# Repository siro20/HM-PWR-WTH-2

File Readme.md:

# HM-PWR-WTH2

Open Source kicad Homematic Homebrew PCB for HmIP-WTH-2.

The PCB supports an input voltage of 3.3V - 36V and generates 2.9V on the
battery emulator clamps. It features a micro USB connector and a JST 2pin
connector.

A LED indicates if the board is working and generates a minimum current
required for stability of the LT3080 regulator.

## Schematics

[HM-PWR-WTH-2.pdf](./HM-PWR-WTH-2/HM-PWR-WTH-2.pdf)

## Pictures

** Mounting plate **

** Assembled **

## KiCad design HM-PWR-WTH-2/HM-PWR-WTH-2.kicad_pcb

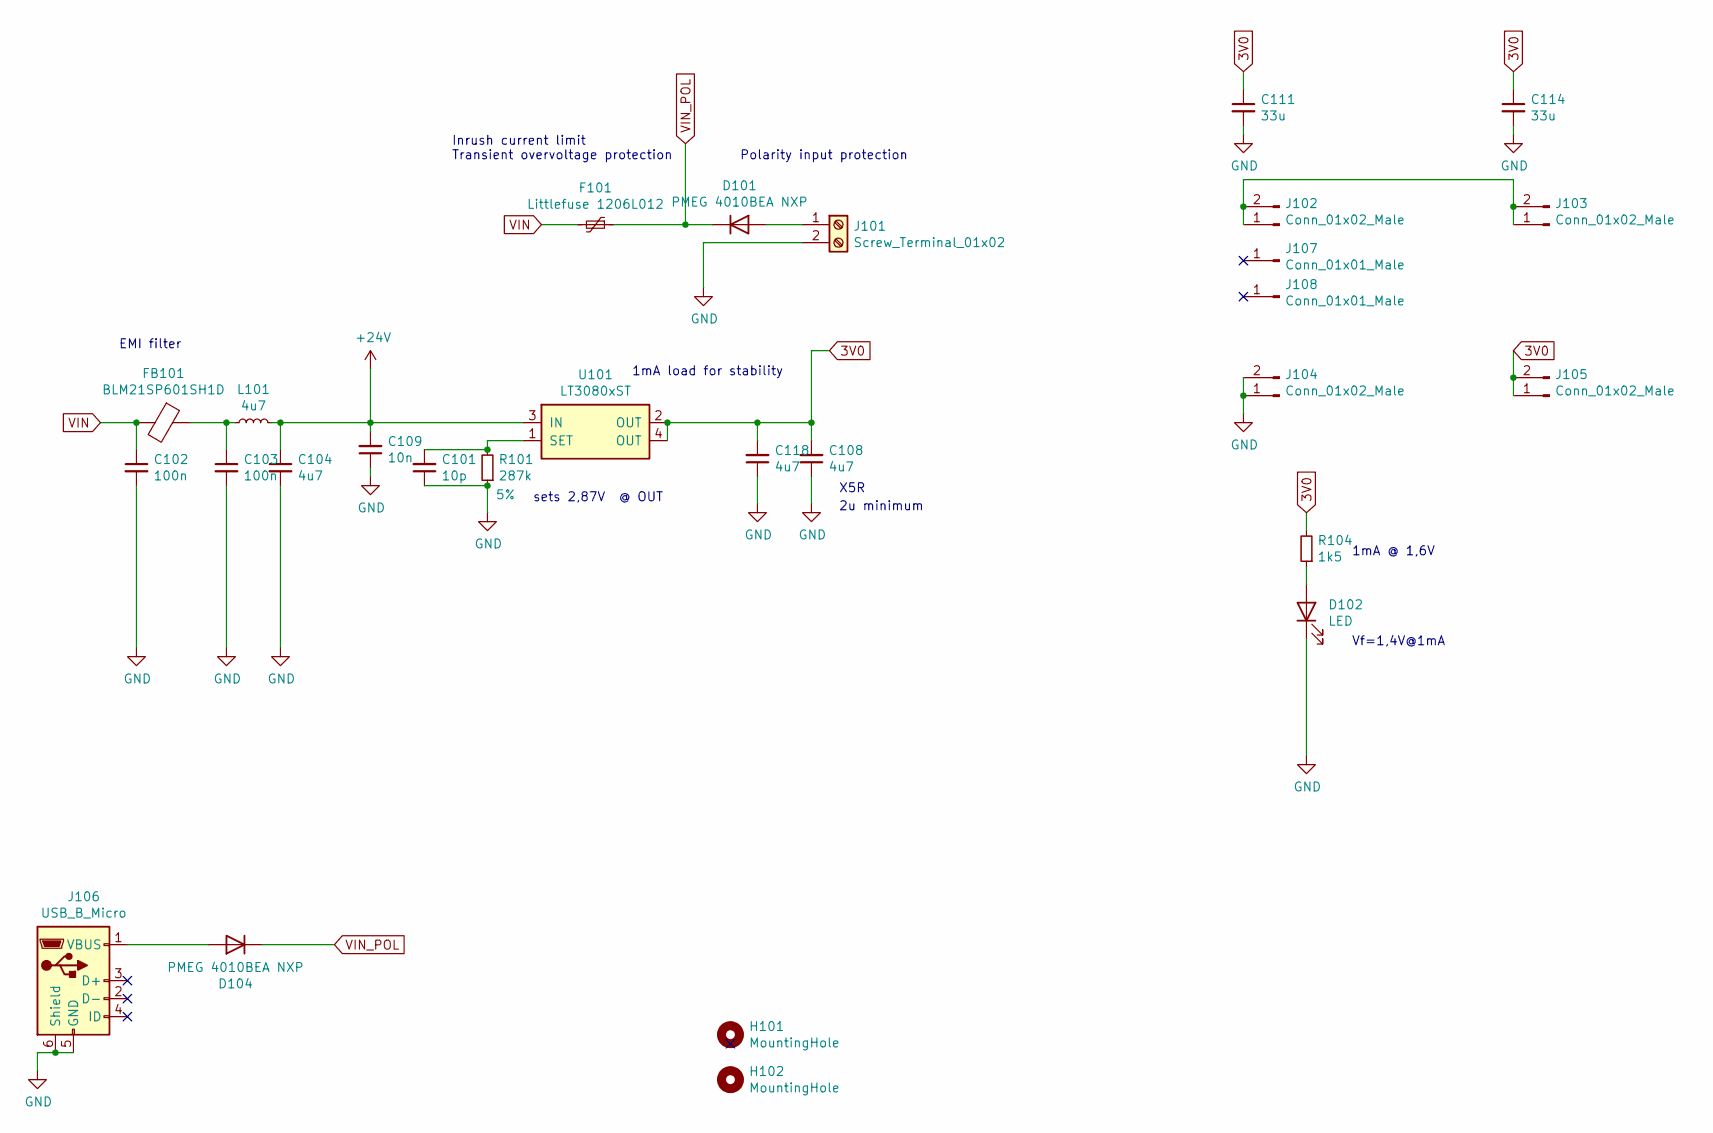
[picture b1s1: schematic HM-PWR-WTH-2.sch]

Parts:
C101: 10p; C_0603_1608Metric
C102: 100n; C_0603_1608Metric_Pad1.08x0.95mm_HandSolder
C103: 100n; C_0805_2012Metric
C104, C108, C118: 4u7; C_1206_3216Metric_Pad1.33x1.80mm_HandSolder
C109: 10n; C_0603_1608Metric_Pad1.08x0.95mm_HandSolder
C111, C114: 33u; C_1812_4532Metric_Pad1.57x3.40mm_HandSolder
D101, D104: PMEG 4010BEA NXP; D_SOD-323
D102: LED; LED_1206_3216Metric
F101: Littlefuse 1206L012; Fuse_1206_3216Metric_Pad1.42x1.75mm_HandSolder
FB101: BLM21SP601SH1D; L_0805_2012Metric_Pad1.15x1.40mm_HandSolder
H101: MountingHole; MountingHole_3.2mm_M3_ISO14580
H102: MountingHole; MountingHole_3.2mm_M3
J101: Screw_Terminal_01x02; JST_PH_B2B-PH-SM4-TB_1x02-1MP_P2.00mm_Vertical
J102, J103, J104, J105: Conn_01x02_Male; Wago_734-132_1x02_P3.50mm_Vertical
J106: USB_B_Micro; USB_Micro-B_GCT_USB3076-30-A
J107, J108: Conn_01x01_Male; Pin_D1.4mm_L8.5mm_W2.8mm_FlatFork
L101: 4u7; L_1210_3225Metric_Pad1.42x2.65mm_HandSolder
R101: 287k; R_0805_2012Metric_Pad1.20x1.40mm_HandSolder; Tolerance 5%
R104: 1k5; R_0805_2012Metric_Pad1.20x1.40mm_HandSolder
U101: LT3080xST; SOT-223

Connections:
3V0: C108.2, C111.1, C114.1, C118.2, J105.1, J105.2, R104.2, U101.2 (OUT), U101.4 (OUT)
+24V: C104.1, C109.2, L101.2, U101.3 (IN)
GND: C101.1, C102.2, C103.2, C104.2, C108.1, C109.1, C111.2, C114.2, C118.1, D102.1 (K), J101.2, J104.1, J104.2, J106.5 (GND), J106.6 (Shield), R101.1
unnamed: C101.2, R101.2, U101.1 (SET)
unnamed: C103.1, FB101.1, L101.1
unnamed: D101.2 (A), J101.1
unnamed: D102.2 (A), R104.1
unnamed: D104.2 (A), J106.1 (VBUS)
unnamed: J102.1, J102.2, J103.1, J103.2
VIN: C102.1, F101.2, FB101.2
VIN_POL: D101.1 (K), D104.1 (K), F101.1

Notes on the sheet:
Inrush current limit Transient overvoltage protection
Polarity input protection
EMI filter
X5R
2u minimum
1mA load for stability
sets 2,87V @ OUT
Vf=1,4V@1mA
1mA @ 1,6V

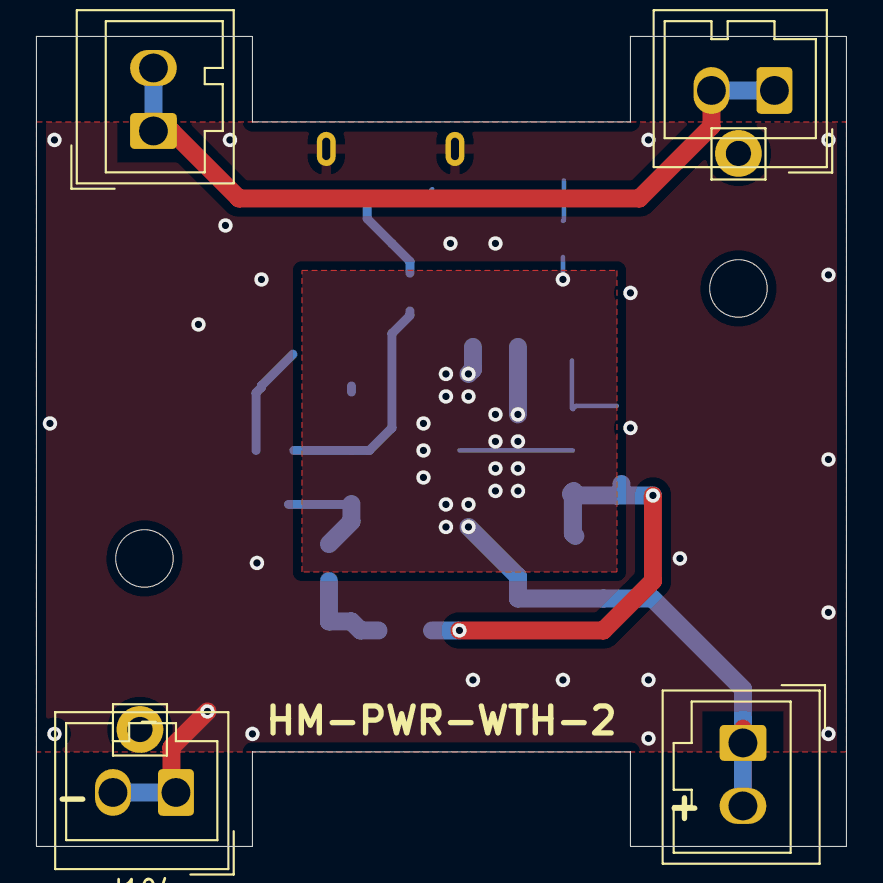
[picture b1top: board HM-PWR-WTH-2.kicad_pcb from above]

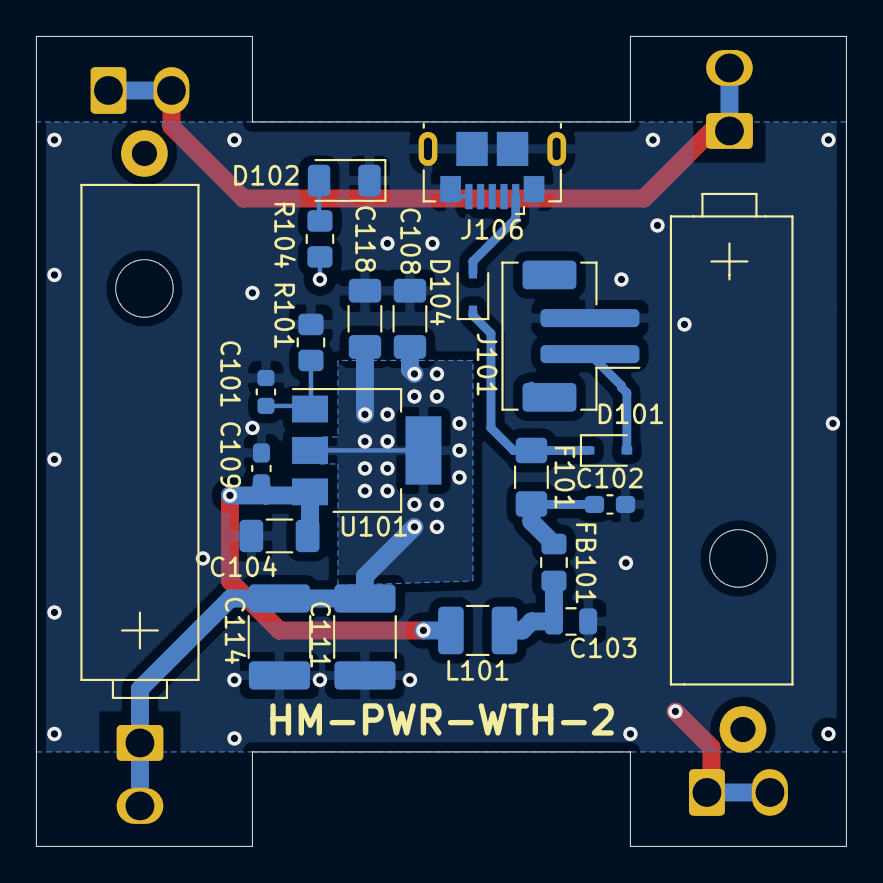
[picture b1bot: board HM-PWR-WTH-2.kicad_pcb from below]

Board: 2 copper layers, 45.0 x 45.0 mm, 28 parts (20 on the bottom side), 11 nets.

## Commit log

2021-04-15 HM-PWR-WTH-2: Finalize the layout
2021-04-18 HM-PWR-WTH-2: Switch to TPS70930
2021-04-18 HM-PWR-WTH-2: Add schmatic and PCB view
2021-05-11 Redesign board
    - Replace regulator with one easier to get in germany
    - Add LED for minimum current draw of 1mA
    - Swap battery + and -
2021-05-14 Redesign board
    - Move all parts to middle and back
    - Use less capacitors
    - Add mounting holes
    - Add battery symbols
2021-05-14 Update PDF and JPEGs
2021-05-31 Update PCB layout
2021-08-01 Add pictures and update Readme
